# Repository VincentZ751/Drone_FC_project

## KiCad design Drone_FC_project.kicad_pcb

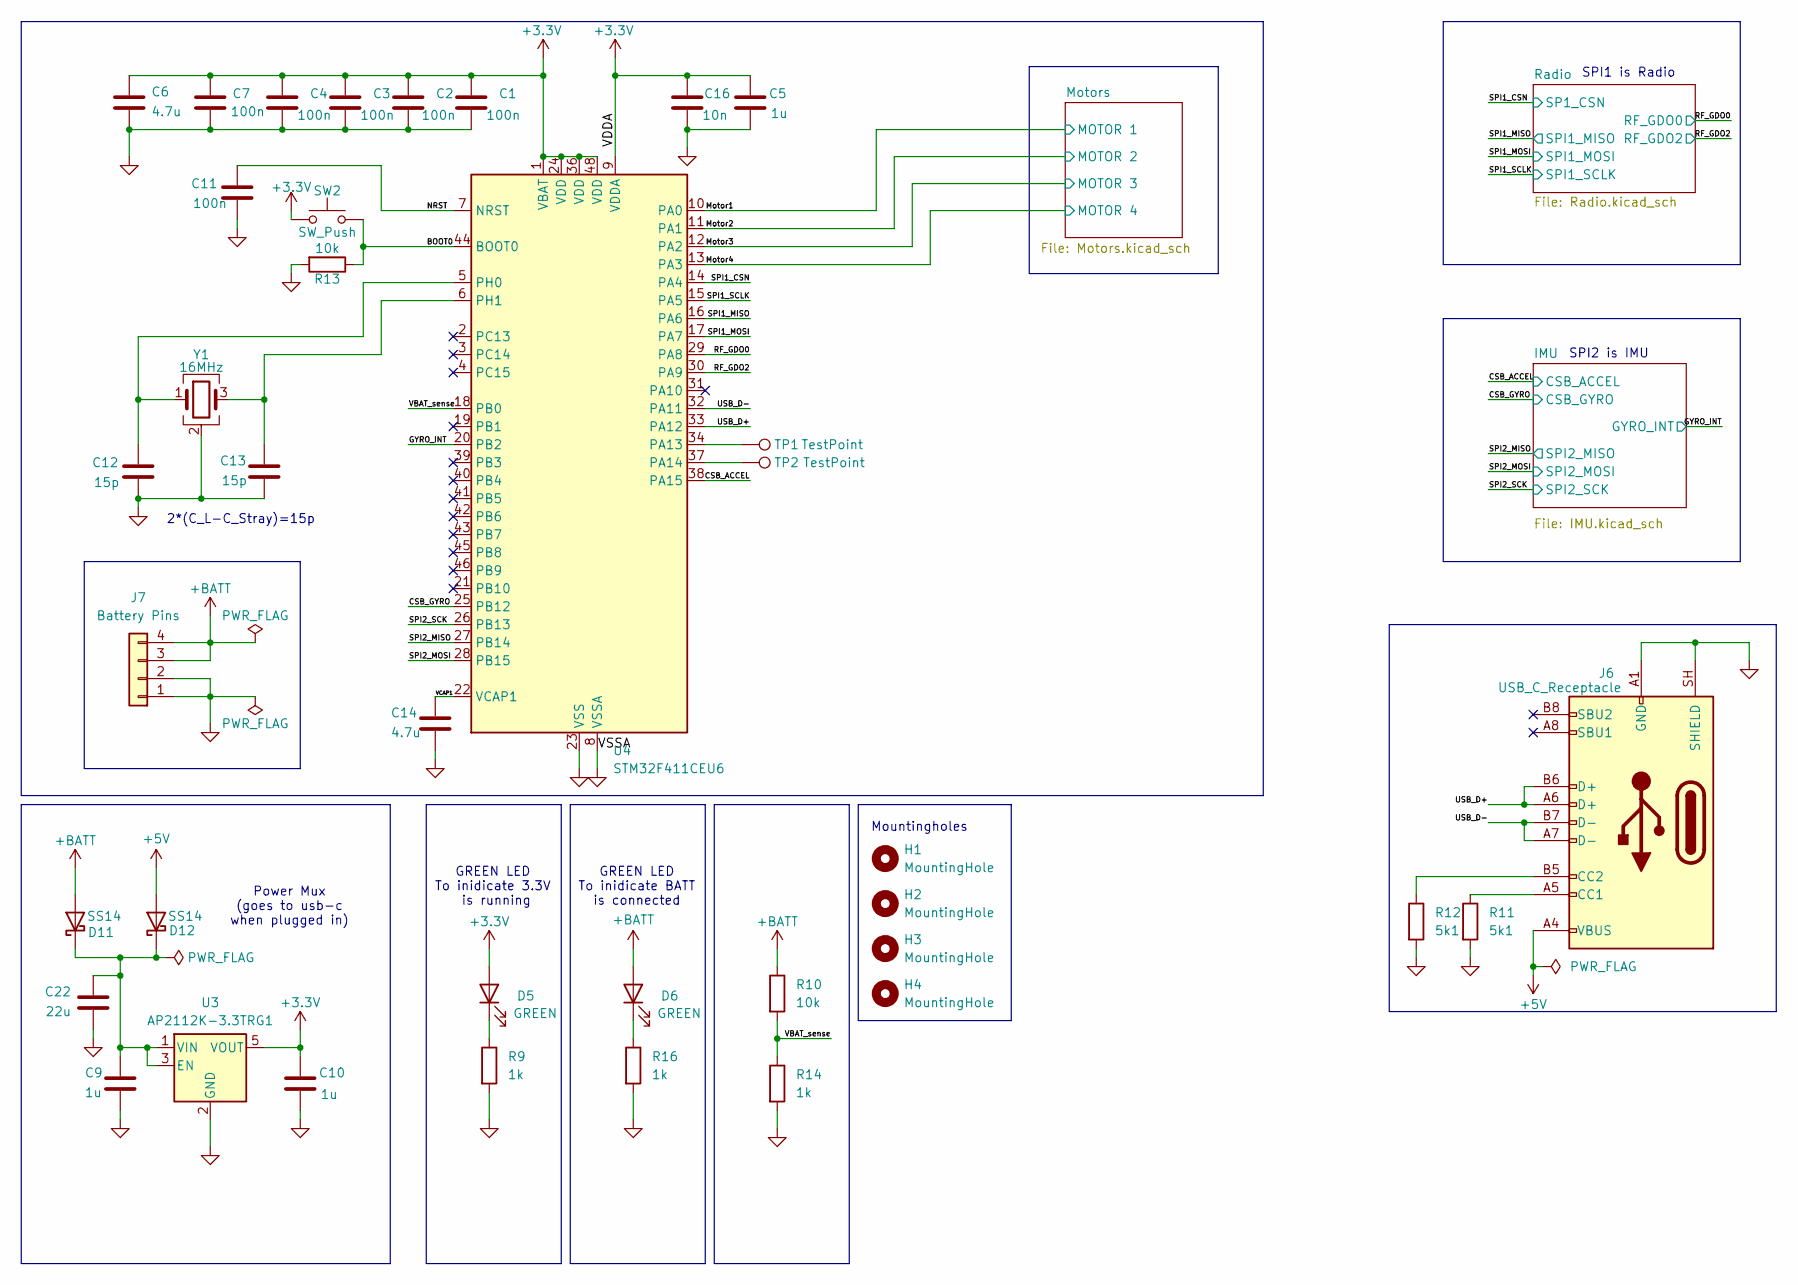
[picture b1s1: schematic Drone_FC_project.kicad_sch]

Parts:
C1, C2, C3, C4, C7, C11: 100n; C_0402_1005Metric
C5, C9, C10: 1u; C_0603_1608Metric
C6, C14: 4.7u; C_0603_1608Metric
C12, C13: 15p; C_0402_1005Metric
C16: 10n; C_0402_1005Metric
C22: 22u; C_0805_2012Metric
D5, D6: GREEN; LED_0603_1608Metric
D11, D12: SS14
H1, H2, H3, H4: MountingHole; MountingHole_2.1mm
J6: USB_C_Receptacle; USB_C_Receptacle_TYPE-C-31-M-12A
J7: Battery Pins; Battery_pin
R9, R14, R16: 1k; R_0402_1005Metric
R10, R13: 10k; R_0402_1005Metric
R11, R12: 5k1; R_0402_1005Metric
SW2: SW_Push; TS-1187A-B-A-B(SPST_button)
TP1, TP2: TestPoint; TestPoint_Pad_D1.0mm
U3: AP2112K-3.3TRG1; SOT-23-5_AP2112K-3.3
U4: STM32F411CEU6; UFQFPN-48_STM32F411CEU6
Y1: 16MHz; Crystal_SMD_3225-4P(16_26MHz)

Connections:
+3.3V: C1.1, C2.1, C3.1, C4.1, C5.1, C6.1, C7.1, C10.1, C16.1, D5.2 (A), SW2.2, U3.5 (VOUT), U4.1 (VBAT), U4.9 (VDDA), U4.24 (VDD), U4.36 (VDD), U4.48 (VDD); also elsewhere on the board
+5V: D12.2 (A), J6.A4 (VBUS), J6.A9 (VBUS), J6.B4 (VBUS), J6.B9 (VBUS)
+BATT: D6.2 (A), D11.2 (A), J7.3, J7.4, R10.1; also elsewhere on the board
/BOOT0: R13.1, SW2.1, U4.44 (BOOT0)
/CSB_ACCEL: U4.38 (PA15); also elsewhere on the board
/CSB_GYRO: U4.25 (PB12); also elsewhere on the board
/GYRO_INT: U4.20 (PB2); also elsewhere on the board
/Motor1: U4.10 (PA0); also elsewhere on the board
/Motor2: U4.11 (PA1); also elsewhere on the board
/Motor3: U4.12 (PA2); also elsewhere on the board
/Motor4: U4.13 (PA3); also elsewhere on the board
/NRST: C11.1, U4.7 (NRST)
/RF_GDO0: U4.29 (PA8); also elsewhere on the board
/RF_GDO2: U4.30 (PA9); also elsewhere on the board
/SPI1_CSN: U4.14 (PA4); also elsewhere on the board
/SPI1_MISO: U4.16 (PA6); also elsewhere on the board
/SPI1_MOSI: U4.17 (PA7); also elsewhere on the board
/SPI1_SCLK: U4.15 (PA5); also elsewhere on the board
/SPI2_MISO: U4.27 (PB14); also elsewhere on the board
/SPI2_MOSI: U4.28 (PB15); also elsewhere on the board
/SPI2_SCK: U4.26 (PB13); also elsewhere on the board
/USB_D+: J6.A6 (D+), J6.B6 (D+), U4.33 (PA12)
/USB_D-: J6.A7 (D-), J6.B7 (D-), U4.32 (PA11)
/VBAT_sense: R10.2, R14.1, U4.18 (PB0)
/VCAP1: C14.1, U4.22 (VCAP1)
GND: C1.2, C2.2, C3.2, C4.2, C5.2, C6.2, C7.2, C9.2, C10.2, C11.2, C12.2, C13.2, C14.2, C16.2, C22.2, J6.A1 (GND), J6.A12 (GND), J6.B1 (GND), J6.B12 (GND), J6.SH (SHIELD), J7.1, J7.2, R9.2, R11.2, R12.2, R13.2, R14.2, R16.2, U3.2 (GND), U4.8 (VSSA), U4.23 (VSS), U4.35 (VSS), U4.47 (VSS), U4.49 (VSS), Y1.2 (G), Y1.4 (G); also elsewhere on the board
unnamed 32: D5.1 (K), R9.1; also elsewhere on the board
unnamed 33: D6.1 (K), R16.1; also elsewhere on the board
unnamed: C9.1, C22.1, D11.1 (K), D12.1 (K), U3.1 (VIN), U3.3 (EN)
unnamed: J6.A5 (CC1), R11.1
unnamed: J6.B5 (CC2), R12.1
unnamed: TP1.1 (1_1), U4.34 (PA13)
unnamed: TP2.1 (1_1), U4.37 (PA14)
unnamed: C12.1, U4.5 (PH0), Y1.1
unnamed: C13.1, U4.6 (PH1), Y1.3

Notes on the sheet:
Power Mux (goes to usb-c when plugged in)
SPI2 is IMU
GREEN LED To inidicate 3.3V is running
Mountingholes
GREEN LED To inidicate BATT is connected
SPI1 is Radio
2*(C_L-C_Stray)=15p

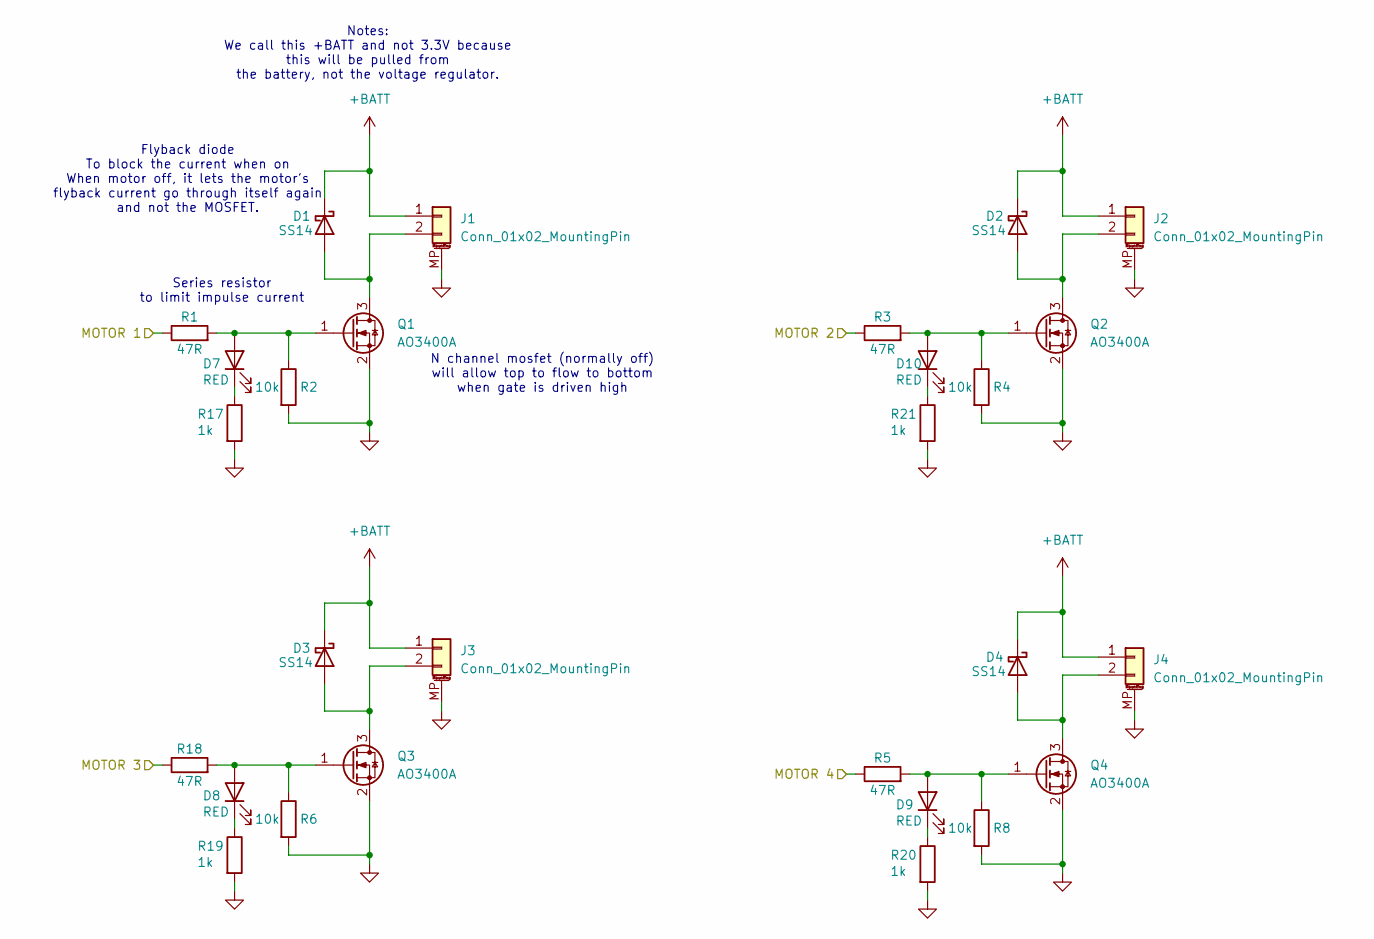
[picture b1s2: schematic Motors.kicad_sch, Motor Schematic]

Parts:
D1, D2, D3, D4: SS14
D7, D8, D9, D10: RED; LED_0603_1608Metric
J1, J2, J3, J4: Conn_01x02_MountingPin; JST_SH_BM02B-SRSS-TB_1x02-1MP_P1.00mm_Vertical
Q1, Q2, Q3, Q4: AO3400A; SOT-23-3_AO3400A
R1, R3, R5, R18: 47R; R_0402_1005Metric
R2, R4, R6, R8: 10k; R_0402_1005Metric
R17, R19, R20, R21: 1k; R_0402_1005Metric

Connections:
+BATT: D1.1 (K), D2.1 (K), D3.1 (K), D4.1 (K), J1.1, J2.1, J3.1, J4.1; also elsewhere on the board
/Motor1: R1.1; also elsewhere on the board
/Motor2: R3.1; also elsewhere on the board
/Motor3: R18.1; also elsewhere on the board
/Motor4: R5.1; also elsewhere on the board
GND: J1.MP (MountPin), J2.MP (MountPin), J3.MP (MountPin), J4.MP (MountPin), Q1.2 (S), Q2.2 (S), Q3.2 (S), Q4.2 (S), R2.2, R4.2, R6.2, R8.2, R17.2, R19.2, R20.2, R21.2; also elsewhere on the board
unnamed: D1.2 (A), J1.2, Q1.3 (D)
unnamed: D2.2 (A), J2.2, Q2.3 (D)
unnamed: D3.2 (A), J3.2, Q3.3 (D)
unnamed: D4.2 (A), J4.2, Q4.3 (D)
unnamed: D7.2 (A), Q1.1 (G), R1.2, R2.1
unnamed: D7.1 (K), R17.1
unnamed: D8.2 (A), Q3.1 (G), R6.1, R18.2
unnamed: D8.1 (K), R19.1
unnamed: D9.2 (A), Q4.1 (G), R5.2, R8.1
unnamed: D9.1 (K), R20.1
unnamed: D10.2 (A), Q2.1 (G), R3.2, R4.1
unnamed: D10.1 (K), R21.1

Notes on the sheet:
Series resistor to limit impulse current
Notes: We call this +BATT and not 3.3V because this will be pulled from the battery, not the voltage regulator.
Flyback diode To block the current when on When motor off, it lets the motor's flyback current go through itself again and not the MOSFET.
N channel mosfet (normally off) will allow top to flow to bottom when gate is driven high

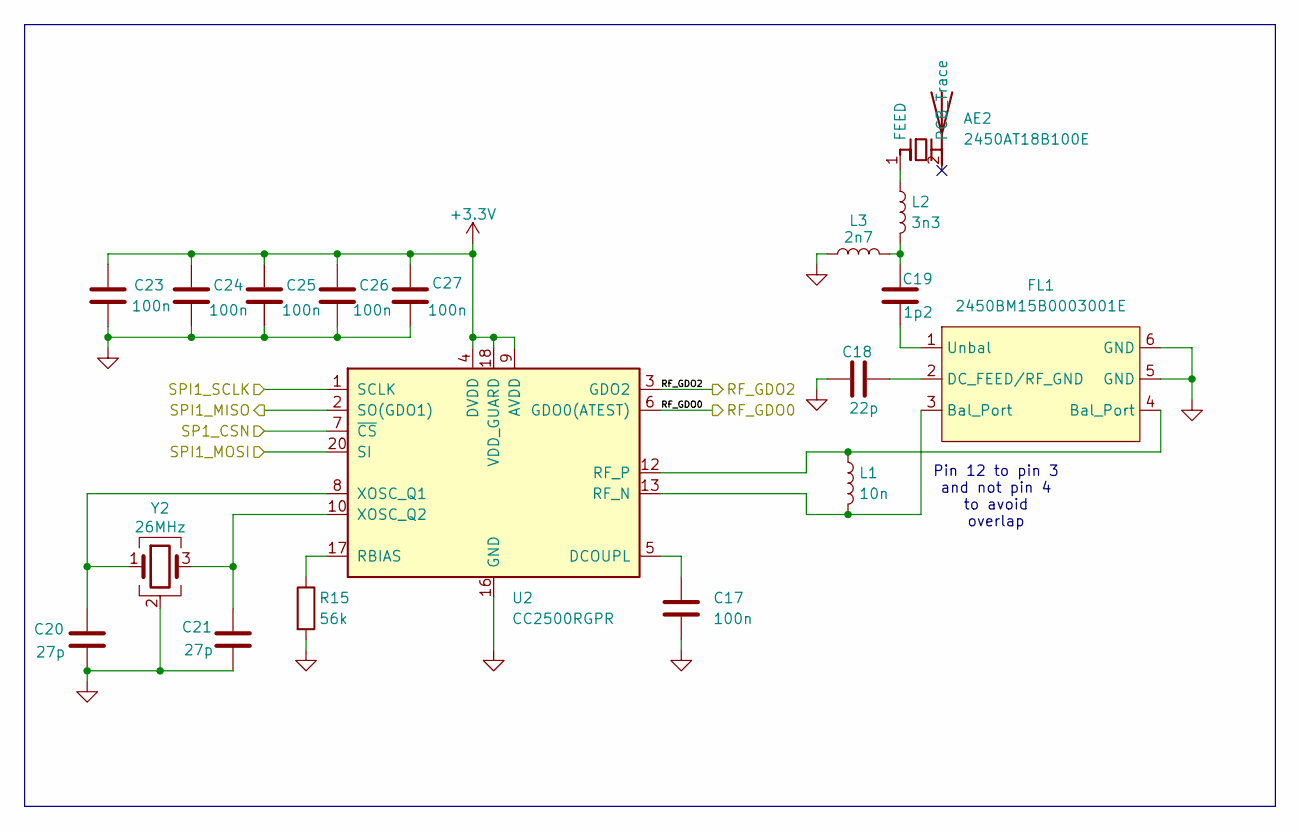
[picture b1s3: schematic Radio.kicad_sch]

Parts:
AE2: 2450AT18B100E; XDCR_2450AT18B100E
C17, C23, C24, C25, C26, C27: 100n; C_0402_1005Metric
C18: 22p; C_0402_1005Metric
C19: 1p2; C_0402_1005Metric
C20, C21: 27p; C_0402_1005Metric
FL1: 2450BM15B0003001E; Balun_Johanson_0896BM15A0001
L1: 10n; L_0402_1005Metric
L2: 3n3; L_0402_1005Metric
L3: 2n7; L_0402_1005Metric
R15: 56k; R_0402_1005Metric
U2: CC2500RGPR; QFN-20_CC2500RGPR
Y2: 26MHz; Crystal_SMD_3225-4P(16_26MHz)

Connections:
+3.3V: C23.1, C24.1, C25.1, C26.1, C27.1, U2.4 (DVDD), U2.9 (AVDD), U2.11 (AVDD), U2.14 (AVDD), U2.15 (AVDD), U2.18 (VDD_GUARD); also elsewhere on the board
/RF_GDO0: U2.6 (GDO0(ATEST)); also elsewhere on the board
/RF_GDO2: U2.3 (GDO2); also elsewhere on the board
/SPI1_CSN: U2.7 (~CS); also elsewhere on the board
/SPI1_MISO: U2.2 (SO(GDO1)); also elsewhere on the board
/SPI1_MOSI: U2.20 (SI); also elsewhere on the board
/SPI1_SCLK: U2.1 (SCLK); also elsewhere on the board
GND: C17.2, C18.1, C20.2, C21.2, C23.2, C24.2, C25.2, C26.2, C27.2, FL1.5 (GND), FL1.6 (GND), L3.1, R15.2, U2.16 (GND), U2.19 (GND), U2.21 (GND), Y2.2 (G), Y2.4 (G); also elsewhere on the board
unnamed: AE2.1 (FEED_1), L2.1
unnamed: C19.2, L2.2, L3.2
unnamed: C18.2, FL1.2 (DC_FEED/RF_GND)
unnamed: C19.1, FL1.1 (Unbal)
unnamed: C17.1, U2.5 (DCOUPL)
unnamed: R15.1, U2.17 (RBIAS)
unnamed: FL1.3 (Bal_Port), L1.2, U2.13 (RF_N)
unnamed: FL1.4 (Bal_Port), L1.1, U2.12 (RF_P)
unnamed: C20.1, U2.8 (XOSC_Q1), Y2.1
unnamed: C21.1, U2.10 (XOSC_Q2), Y2.3

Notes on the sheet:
Pin 12 to pin 3 and not pin 4 to avoid overlap

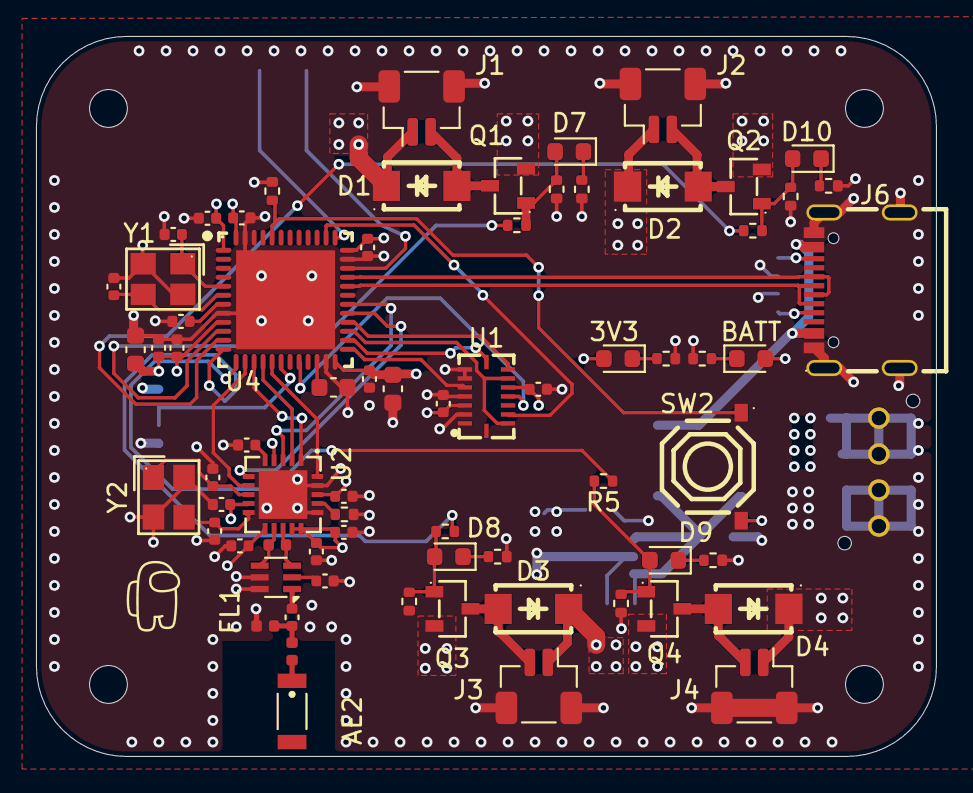
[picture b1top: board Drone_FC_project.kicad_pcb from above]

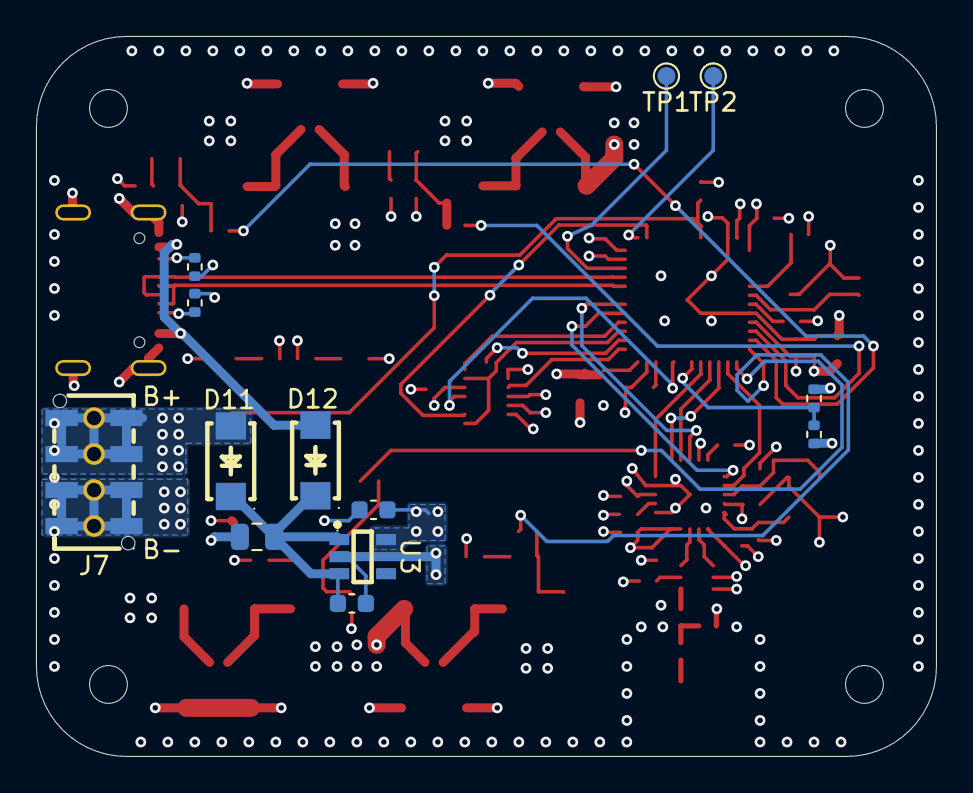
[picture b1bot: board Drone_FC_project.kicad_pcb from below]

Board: 4 copper layers, 50.0 x 40.0 mm, 87 parts (13 on the bottom side), 57 nets.

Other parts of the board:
3V3: GREEN; LED_0603_1608Metric
BATT: GREEN; LED_0603_1608Metric
C8, C15: 100n; C_0402_1005Metric
U1: BMI088; LGA-16_Bosch_BMI088

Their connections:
+3.3V: 3V3.2 (A), C8.1, C15.1, U1.3 (VDD), U1.11 (VDDIO); also elsewhere on the board
+BATT: BATT.2 (A); also elsewhere on the board
/CSB_ACCEL: U1.14 (~CSB1); also elsewhere on the board
/CSB_GYRO: U1.5 (~CSB2); also elsewhere on the board
/GYRO_INT: U1.12 (INT3); also elsewhere on the board
/SPI2_MISO: U1.10 (SDO2), U1.15 (SDO1); also elsewhere on the board
/SPI2_MOSI: U1.9 (SDI/SDA); also elsewhere on the board
/SPI2_SCK: U1.8 (SCK/SCL); also elsewhere on the board
GND: C8.2, C15.2, U1.2 (GNDA), U1.4 (GNDA), U1.6 (GNDIO), U1.7 (PS); also elsewhere on the board
unnamed 32: 3V3.1 (K); also elsewhere on the board
unnamed 33: BATT.1 (K); also elsewhere on the board

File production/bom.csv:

Designator,Footprint,Quantity,Value,LCSC Part #
"3V3, BATT",0603,2,GREEN,
AE2,XDCR_2450AT18B100E,1,2450AT18B100E,
"C1, C11, C15, C17, C2, C23, C24, C25, C26, C27, C3, C4, C7, C8",0402,14,100n,
"C10, C5, C9",0603,3,1u,
"C12, C13",0402,2,15p,
"C14, C6",0603,2,4.7u,
"C16, L1",0402,2,10n,
C18,0402,1,22p,
C19,0402,1,1p2,
"C20, C21",0402,2,27p,
C22,0805,1,22u,
"D1, D11, D12, D2, D3, D4",SS14,6,SS14,C2480
"D10, D7, D8, D9",0603,4,RED,
FL1,Balun_Johanson_0896BM15A0001,1,2450BM15B0003001E,
"J1, J2, J3, J4",JST_SH_BM02B-SRSS-TB_1x02-1MP_P1.00mm_Vertical,4,Conn_01x02_MountingPin,
J6,USB_C_Receptacle_TYPE-C-31-M-12A,1,USB_C_Receptacle,C5337088
J7,Battery_pin,1,Battery Pins,C39833032
L2,0402,1,3n3,
L3,0402,1,2n7,
"Q1, Q2, Q3, Q4",SOT-23-3_AO3400A,4,AO3400A,C20917
"R1, R18, R3, R5",0402,4,47R,
"R10, R13, R2, R4, R6, R8",0402,6,10k,
"R11, R12",0402,2,5k1,
"R14, R16, R17, R19, R20, R21, R9",0402,7,1k,
R15,0402,1,56k,
SW2,TS-1187A-B-A-B(SPST_button),1,SW_Push,C318884
"TP1, TP2",TestPoint_Pad_D1.0mm,2,TestPoint,
U1,LGA-16_Bosch_BMI088,1,BMI088,C194919
U2,QFN-20_CC2500RGPR,1,CC2500RGPR,C57494
U3,SOT-23-5_AP2112K-3.3,1,AP2112K-3.3TRG1,C51118
U4,UFQFPN-48_STM32F411CEU6,1,STM32F411CEU6,C60420
Y1,Crystal_SMD_3225-4P(16_26MHz),1,16MHz,C70573
Y2,Crystal_SMD_3225-4P(16_26MHz),1,26MHz,C70573

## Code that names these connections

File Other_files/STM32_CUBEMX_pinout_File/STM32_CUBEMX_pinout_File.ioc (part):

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Mcu.Name=STM32F411C(C-E)Ux
Mcu.Package=UFQFPN48
Mcu.UserName=STM32F411CEUx
PA0-WKUP.Signal=S_TIM2_CH1_ETR
PA1.Signal=S_TIM2_CH2
PA11.Mode=Host_Only
PA11.Signal=USB_OTG_FS_DM
PA12.Mode=Host_Only
PA12.Signal=USB_OTG_FS_DP
PA13.Mode=Serial_Wire
PA13.Signal=SYS_JTMS-SWDIO
PA14.Mode=Serial_Wire
PA14.Signal=SYS_JTCK-SWCLK
PA15.Signal=GPIO_Output
PA2.Signal=S_TIM2_CH3
PA3.Signal=S_TIM2_CH4
PA5.Mode=Full_Duplex_Master
PA5.Signal=SPI1_SCK
PA6.Mode=Full_Duplex_Master
PA6.Signal=SPI1_MISO
PA7.Mode=Full_Duplex_Master
PA7.Signal=SPI1_MOSI
PA8.Signal=GPIO_Output
PA9.Signal=GPIO_Output
PB10.Signal=GPXTI10
PB12.Signal=GPIO_Output
PB13.Mode=Full_Duplex_Master
PB13.Signal=SPI2_SCK
PB14.Mode=Full_Duplex_Master
PB14.Signal=SPI2_MISO
PB15.Mode=Full_Duplex_Master
PB15.Signal=SPI2_MOSI
PB2.Signal=GPIO_Output
PH0\ -\ OSC_IN.Mode=HSE-External-Oscillator
PH0\ -\ OSC_IN.Signal=RCC_OSC_IN
PH1\ -\ OSC_OUT.Mode=HSE-External-Oscillator
PH1\ -\ OSC_OUT.Signal=RCC_OSC_OUT
RCC.HSE_VALUE=8000000
RCC.SYSCLKFreq_VALUE=16000000
board=custom
